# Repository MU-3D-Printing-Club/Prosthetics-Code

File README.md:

# Prosthetics-Code

Where people who are moderately okay at programming but also in the 3D Printing club work together.

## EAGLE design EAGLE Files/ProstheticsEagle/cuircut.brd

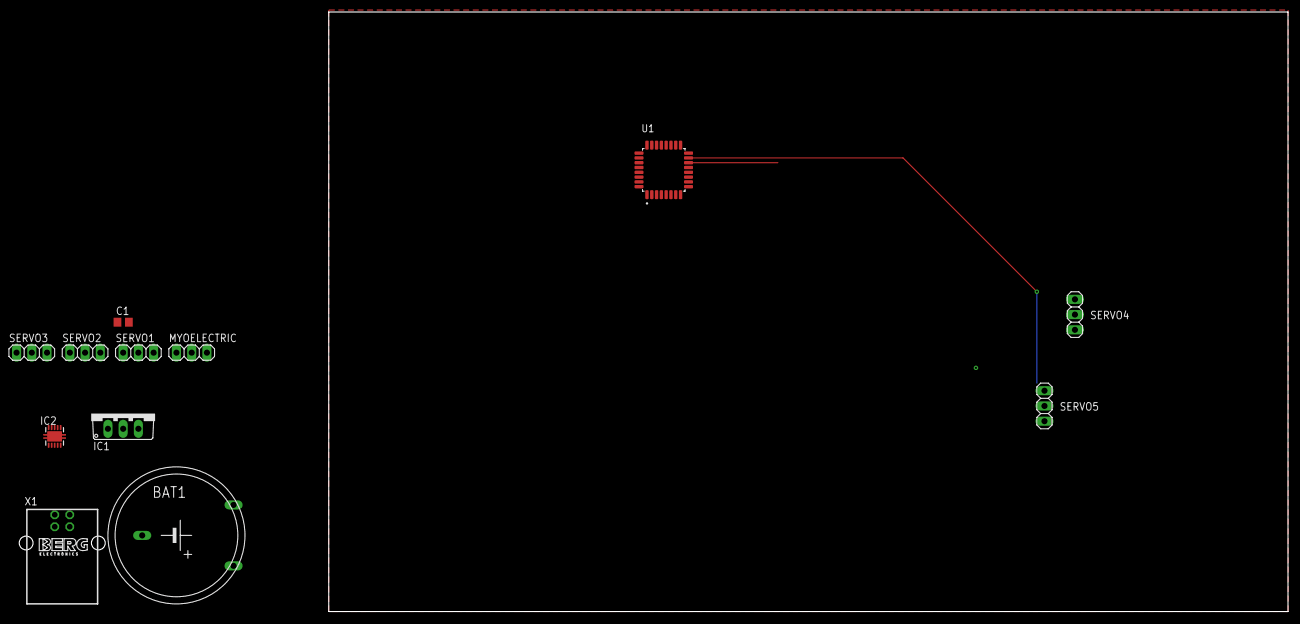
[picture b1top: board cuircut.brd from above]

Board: 2 copper layers, 160.0 x 100.0 mm, 12 parts (0 on the bottom side), 9 nets.

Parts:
BAT1: BATTERY
C1: C0805
IC1: 786TV; TO220V
IC2: BQ24022; DRC-S-PVSON-N10
MYOELECTRIC: 1X03
SERVO1, SERVO2, SERVO3, SERVO4, SERVO5: 1X03
U1: ATMEGA328P-AU; TQFP-32
X1: PN61729

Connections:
AGND: BAT1.-, C1.2, IC1.2, IC2.5, IC2.6, MYOELECTRIC.2, SERVO1.3, SERVO2.3, SERVO3.3, SERVO4.3, SERVO5.3, U1.3, X1.2
unnamed: BAT1.+, IC1.1, IC2.10
unnamed: IC2.3, U1.29
unnamed: IC2.8, U1.17
unnamed: C1.1, IC2.2, X1.1
unnamed: MYOELECTRIC.3, U1.24
POWER: IC1.3, SERVO1.2, SERVO3.2, U1.4
SIGNAL1: SERVO1.1, U1.13
SIGNAL2: SERVO2.1, U1.14

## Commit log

2019-09-14 test update
    added code vital to the success of the project
2019-09-15 A second update
    even more useful than last time
2019-09-20 Jared's first change
2019-09-24 Added in a button, moved the active code in if statement if button==high
2019-10-03 import format
    adjusting formatting
2019-10-11 reframe for multiple gestures, need to set functions to set position and new wiring
2019-10-11 concept average function
2019-10-11 dowhile to allow for multiple attempts
2019-10-11 cleaned up state initialization
2019-10-11 reversed conditions since now using else to improve runtime
2019-10-11 redid prints in accordance to Serial.println method arguments
2019-10-11 update so it will state second then wait
2019-10-11 default position
2019-10-11 initialize only once to avoid reinitializaiton in the loop
2019-10-11 added servo adjustments
2019-10-11 remove old functions
2019-10-11 fully debugged and tested
2019-10-13 added comments
2019-10-13 finished comment
2019-10-29 First boi
2019-11-08 Adjusted the setTrigger function
    Changed the function to now collect a reading of the flex several times in a three second span, does this three seperate times and returns the average from these three trials.
2019-11-10 setTrigger() now looks for local maxes before comparing with the current absolute max
2019-11-10 setTrigger() to be more precise
    Added variables to easily tweak intervals and time of trials. Also made the interval for each reading smaller so more information is collected for more accurate triggers
2019-11-15 Added Folder and Started Messing with Charging State functions
2019-11-17 color changing LED should now change color and relect charging status
2019-11-17 Deleted that
2019-11-17 renamed
2019-11-17 Update myoFlex.ino
    New SetTrigger function
2019-11-17 Added Button Inturrupt
2019-11-17 Updated Code
2019-12-04 Added test flex
2019-12-05 updated pin numbers for new board
2019-12-05 refactored some code to be more readable
2019-12-05 ran astyle with default settings to help fix formatting mess
2019-12-05 fixed accidental logic change from cleanup
2019-12-06 BatteryCheck
    first test of checking battery
2019-12-09 added testFlex
2019-12-13 started work on interupts
2019-12-13 fixed serial printing
2019-12-13 interupts blinking led 1hz
2019-12-13 setting led from vbat voltage (not 100% all the time)
2019-12-15 prevent battery double press and blink led purple when calibrating
2019-12-15 fix led color and make sure it's off on startup
2019-12-15 disable motors if battery is low
2019-12-15 removed delay from locked() and refactored a tiny bit
2019-12-16 changed calibration led color, added more debug output
2019-12-17 disabled motor low power disable. tweaks to led color code. default state is open if state broken.
2019-12-19 swaped thumb and pinky pins
